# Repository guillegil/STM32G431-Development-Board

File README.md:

# STM32G431 Development Board

KiCad 10 design files for a small development board based on the STMicroelectronics
STM32G431CBT6 microcontroller (Cortex-M4F, 170 MHz, 128 KB flash, USB).

This is a personal learning project — my first custom-designed PCB, built as
preparation for a more complex nRF5340-based wireless keyboard development board.

## Features

- STM32G431CBT6 in LQFP-48 package (hand-solderable)
- USB-C connector for power and native USB device communication
- 3.3 V LDO regulator
- SWD programming header
- UART debug header
- User LED + user button
- Reset button + boot-mode jumper
- GPIO breakout headers for experimentation

## Project goals

- Learn KiCad 10 schematic and PCB design workflow
- Learn home reflow soldering (hot plate + hot air)
- Build a base for future Zephyr RTOS experimentation
- Prepare skills for a larger custom-keyboard project

## Status

🟡 In design — schematic in progress

## Tools used

- KiCad 10.x
- Zephyr RTOS / nRF Connect SDK (firmware, future)
- JLCPCB (PCB fabrication, planned)

## License

See [LICENSE](LICENSE). This project is open source under the MIT License.

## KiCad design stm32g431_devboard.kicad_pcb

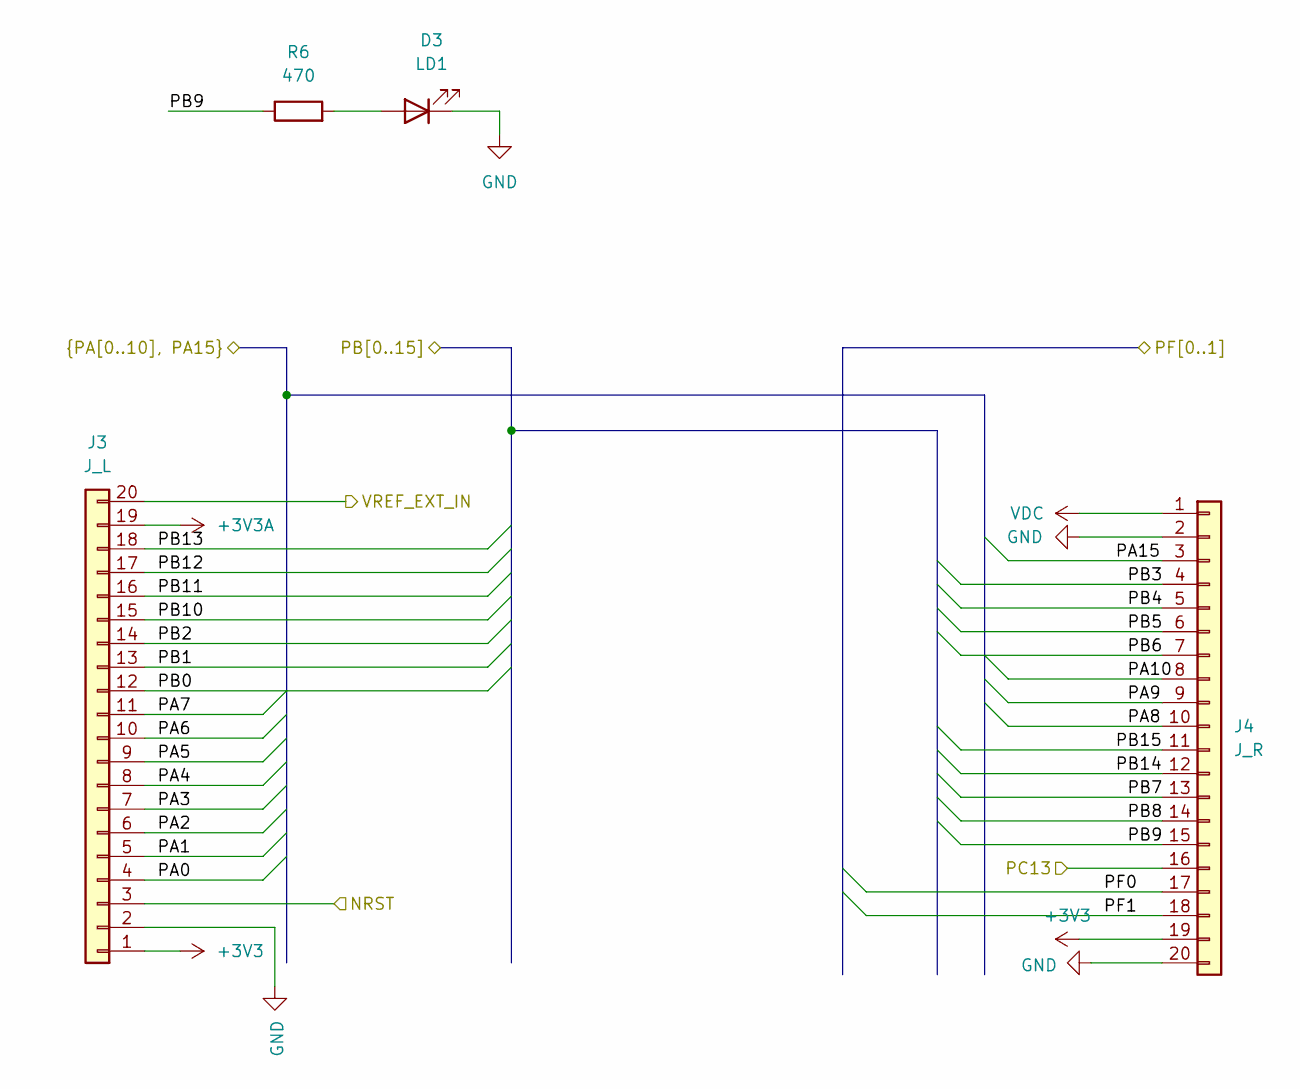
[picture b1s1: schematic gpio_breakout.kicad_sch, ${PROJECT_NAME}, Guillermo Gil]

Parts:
D3: LD1; LED_0603_1608Metric_Pad1.05x0.95mm_HandSolder
J3: J_L; PinHeader_1x20_P2.54mm_Vertical
J4: J_R; PinHeader_1x20_P2.54mm_Vertical
R6: 470; R_0603_1608Metric_Pad0.98x0.95mm_HandSolder

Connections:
+3V3: J3.1, J4.19; also elsewhere on the board
+3V3A: J3.19; also elsewhere on the board
/GPIO Breakout/PA0: J3.4; also elsewhere on the board
/GPIO Breakout/PA1: J3.5; also elsewhere on the board
/GPIO Breakout/PA2: J3.6; also elsewhere on the board
/GPIO Breakout/PA3: J3.7; also elsewhere on the board
/GPIO Breakout/PA4: J3.8; also elsewhere on the board
/GPIO Breakout/PA5: J3.9; also elsewhere on the board
/GPIO Breakout/PA6: J3.10; also elsewhere on the board
/GPIO Breakout/PA7: J3.11; also elsewhere on the board
/GPIO Breakout/PA8: J4.10; also elsewhere on the board
/GPIO Breakout/PA9: J4.9; also elsewhere on the board
/GPIO Breakout/PA10: J4.8; also elsewhere on the board
/GPIO Breakout/PA15: J4.3; also elsewhere on the board
/GPIO Breakout/PB0: J3.12; also elsewhere on the board
/GPIO Breakout/PB1: J3.13; also elsewhere on the board
/GPIO Breakout/PB2: J3.14; also elsewhere on the board
/GPIO Breakout/PB3: J4.4; also elsewhere on the board
/GPIO Breakout/PB4: J4.5; also elsewhere on the board
/GPIO Breakout/PB5: J4.6; also elsewhere on the board
/GPIO Breakout/PB6: J4.7; also elsewhere on the board
/GPIO Breakout/PB7: J4.13; also elsewhere on the board
/GPIO Breakout/PB8: J4.14; also elsewhere on the board
/GPIO Breakout/PB9: J4.15, R6.1; also elsewhere on the board
/GPIO Breakout/PB10: J3.15; also elsewhere on the board
/GPIO Breakout/PB11: J3.16; also elsewhere on the board
/GPIO Breakout/PB12: J3.17; also elsewhere on the board
/GPIO Breakout/PB13: J3.18; also elsewhere on the board
/GPIO Breakout/PB14: J4.12; also elsewhere on the board
/GPIO Breakout/PB15: J4.11; also elsewhere on the board
/GPIO Breakout/PF0: J4.17; also elsewhere on the board
/GPIO Breakout/PF1: J4.18; also elsewhere on the board
/GPIO Breakout/VREF_EXT_IN: J3.20; also elsewhere on the board
/MCU/NRST: J3.3; also elsewhere on the board
/MCU/PC13: J4.16; also elsewhere on the board
GND: D3.1 (K), J3.2, J4.2, J4.20; also elsewhere on the board
unnamed: D3.2 (A), R6.2
VDC: J4.1; also elsewhere on the board

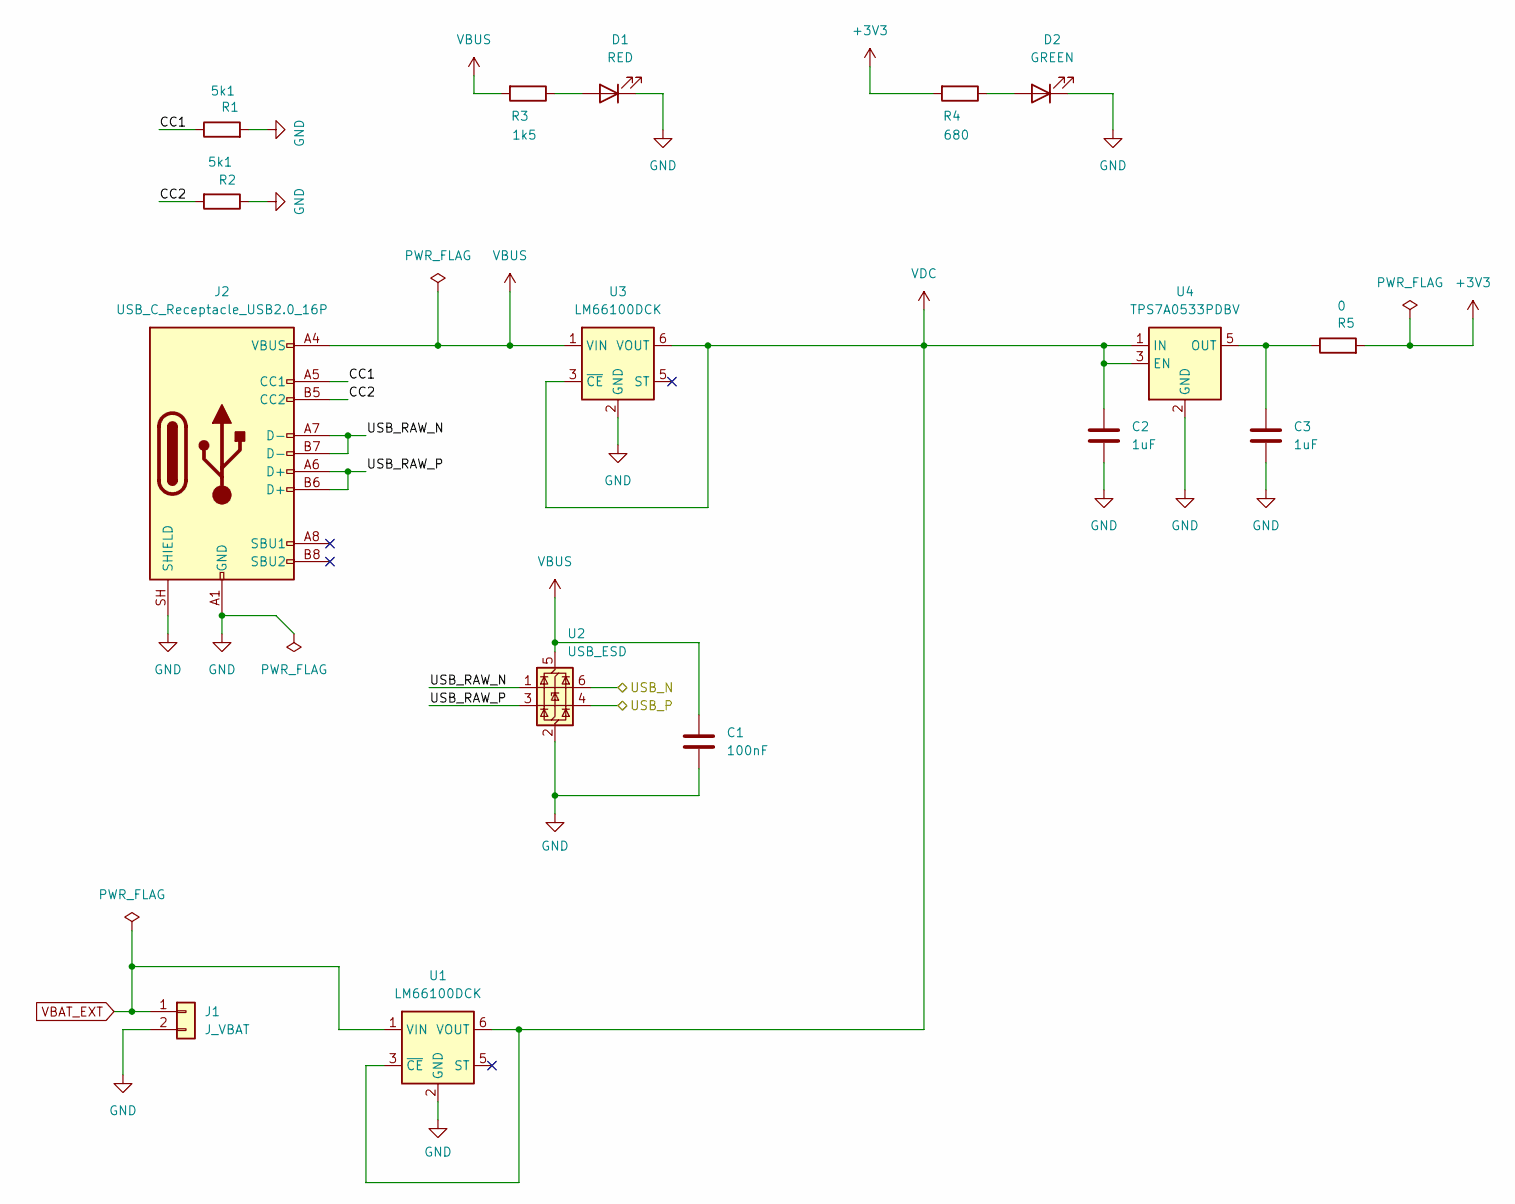
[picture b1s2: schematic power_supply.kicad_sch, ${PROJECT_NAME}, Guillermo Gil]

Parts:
C1: 100nF; C_0603_1608Metric_Pad1.08x0.95mm_HandSolder
C2, C3: 1uF; C_0603_1608Metric_Pad1.08x0.95mm_HandSolder
D1: RED; LED_0603_1608Metric_Pad1.05x0.95mm_HandSolder
D2: GREEN; LED_0603_1608Metric_Pad1.05x0.95mm_HandSolder
J1: J_VBAT; PinHeader_1x02_P2.54mm_Vertical
J2: USB_C_Receptacle_USB2.0_16P; USB_C_Receptacle_GCT_USB4085
R1, R2: 5k1; R_0603_1608Metric_Pad0.98x0.95mm_HandSolder
R3: 1k5; R_0603_1608Metric_Pad0.98x0.95mm_HandSolder
R4: 680; R_0603_1608Metric_Pad0.98x0.95mm_HandSolder
R5: 0; R_0603_1608Metric_Pad0.98x0.95mm_HandSolder
U1, U3: LM66100DCK; SOT-363_SC-70-6
U2: USB_ESD; SOT-23-6
U4: TPS7A0533PDBV; SOT-23-5_HandSoldering

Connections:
+3V3: R4.2, R5.2; also elsewhere on the board
/MCU/USB_N: U2.6 (I/O1); also elsewhere on the board
/MCU/USB_P: U2.4 (I/O2); also elsewhere on the board
/Power Supply/CC1: J2.A5 (CC1), R1.1
/Power Supply/CC2: J2.B5 (CC2), R2.2
/Power Supply/USB_RAW_N: J2.A7 (D-), J2.B7 (D-), U2.1 (I/O1)
/Power Supply/USB_RAW_P: J2.A6 (D+), J2.B6 (D+), U2.3 (I/O2)
GND: C1.2, C2.2, C3.2, D1.1 (K), D2.1 (K), J1.2, J2.A1 (GND), J2.A12 (GND), J2.B1 (GND), J2.B12 (GND), J2.SH (SHIELD), R1.2, R2.1, U1.2 (GND), U2.2 (GND), U3.2 (GND), U4.2 (GND); also elsewhere on the board
unnamed: D1.2 (A), R3.1
unnamed: D2.2 (A), R4.1
unnamed: C3.1, R5.1, U4.5 (OUT)
VBAT_EXT: J1.1, U1.1 (VIN)
VBUS: C1.1, J2.A4 (VBUS), J2.A9 (VBUS), J2.B4 (VBUS), J2.B9 (VBUS), R3.2, U2.5 (VBUS), U3.1 (VIN)
VDC: C2.1, U1.3 (~CE), U1.6 (VOUT), U3.3 (~CE), U3.6 (VOUT), U4.1 (IN), U4.3 (EN); also elsewhere on the board

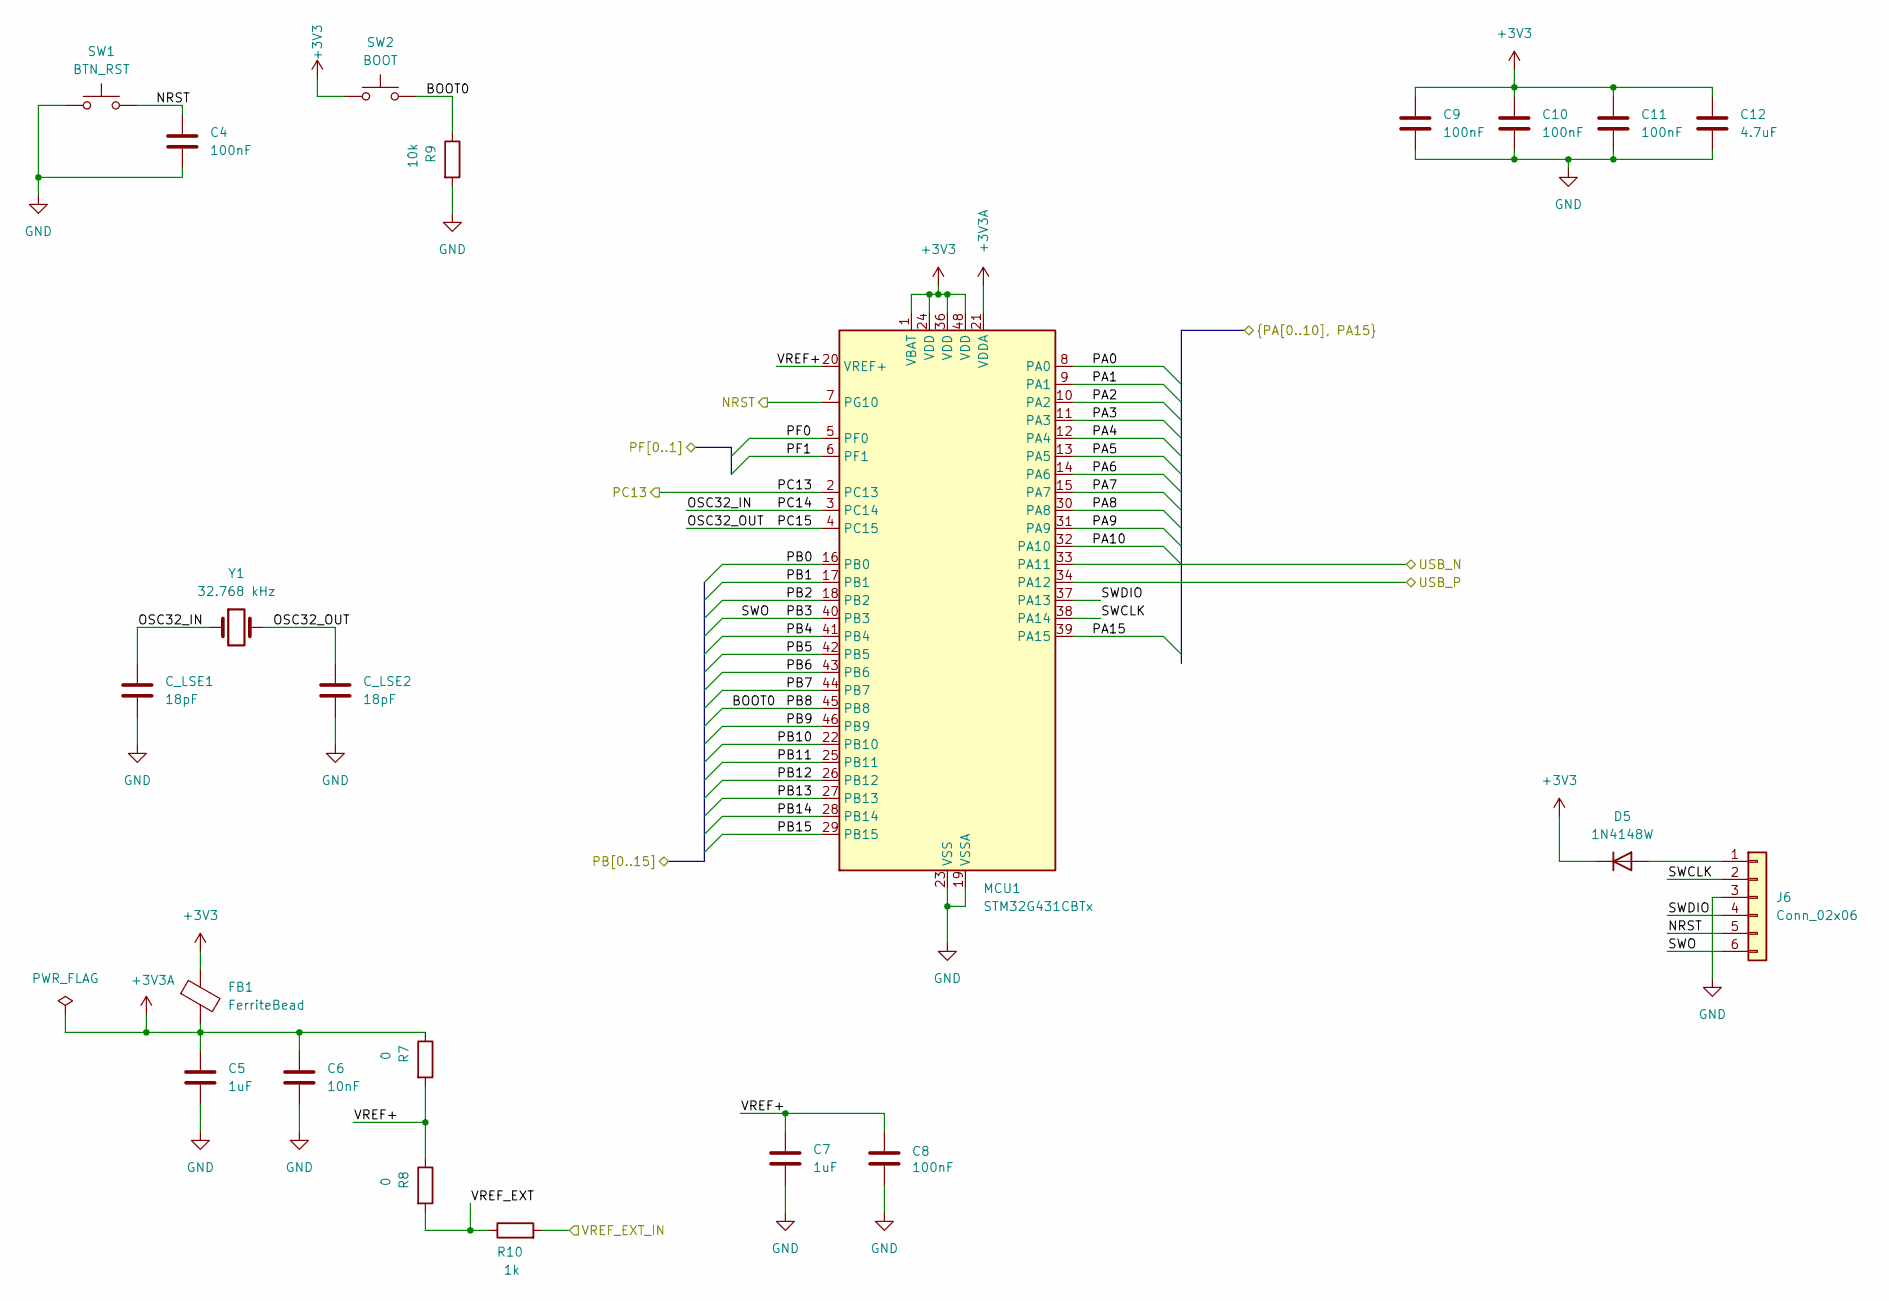
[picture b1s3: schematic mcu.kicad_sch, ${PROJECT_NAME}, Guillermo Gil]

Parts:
C4, C8, C9, C10, C11: 100nF; C_0603_1608Metric_Pad1.08x0.95mm_HandSolder
C5, C7: 1uF; C_0603_1608Metric_Pad1.08x0.95mm_HandSolder
C6: 10nF; C_0603_1608Metric_Pad1.08x0.95mm_HandSolder
C12: 4.7uF; C_0603_1608Metric_Pad1.08x0.95mm_HandSolder
C_LSE1, C_LSE2: 18pF; C_0603_1608Metric_Pad1.08x0.95mm_HandSolder
D5: 1N4148W; D_SOD-323
FB1: FerriteBead; L_0603_1608Metric_Pad1.05x0.95mm_HandSolder
J6: Conn_02x06; PinHeader_2x03_P2.54mm_Vertical_SMD
MCU1: STM32G431CBTx; LQFP-48_7x7mm_P0.5mm
R7, R8: 0; R_0603_1608Metric_Pad0.98x0.95mm_HandSolder
R9: 10k; R_0603_1608Metric_Pad0.98x0.95mm_HandSolder
R10: 1k; R_0603_1608Metric_Pad0.98x0.95mm_HandSolder
SW1: BTN_RST; SW_SPST_PTS810
SW2: BOOT; SW_SPST_PTS810
Y1: 32.768 kHz; Crystal_SMD_3215-2Pin_3.2x1.5mm

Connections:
+3V3: C9.1, C10.1, C11.1, C12.1, D5.1 (K), FB1.1, MCU1.1 (VBAT), MCU1.24 (VDD), MCU1.36 (VDD), MCU1.48 (VDD), SW2.1; also elsewhere on the board
+3V3A: C5.1, C6.1, FB1.2, MCU1.21 (VDDA), R7.1; also elsewhere on the board
/GPIO Breakout/PA0: MCU1.8 (PA0); also elsewhere on the board
/GPIO Breakout/PA1: MCU1.9 (PA1); also elsewhere on the board
/GPIO Breakout/PA2: MCU1.10 (PA2); also elsewhere on the board
/GPIO Breakout/PA3: MCU1.11 (PA3); also elsewhere on the board
/GPIO Breakout/PA4: MCU1.12 (PA4); also elsewhere on the board
/GPIO Breakout/PA5: MCU1.13 (PA5); also elsewhere on the board
/GPIO Breakout/PA6: MCU1.14 (PA6); also elsewhere on the board
/GPIO Breakout/PA7: MCU1.15 (PA7); also elsewhere on the board
/GPIO Breakout/PA8: MCU1.30 (PA8); also elsewhere on the board
/GPIO Breakout/PA9: MCU1.31 (PA9); also elsewhere on the board
/GPIO Breakout/PA10: MCU1.32 (PA10); also elsewhere on the board
/GPIO Breakout/PA15: MCU1.39 (PA15); also elsewhere on the board
/GPIO Breakout/PB0: MCU1.16 (PB0); also elsewhere on the board
/GPIO Breakout/PB1: MCU1.17 (PB1); also elsewhere on the board
/GPIO Breakout/PB2: MCU1.18 (PB2); also elsewhere on the board
/GPIO Breakout/PB3: J6.6, MCU1.40 (PB3); also elsewhere on the board
/GPIO Breakout/PB4: MCU1.41 (PB4); also elsewhere on the board
/GPIO Breakout/PB5: MCU1.42 (PB5); also elsewhere on the board
/GPIO Breakout/PB6: MCU1.43 (PB6); also elsewhere on the board
/GPIO Breakout/PB7: MCU1.44 (PB7); also elsewhere on the board
/GPIO Breakout/PB8: MCU1.45 (PB8), R9.1, SW2.2; also elsewhere on the board
/GPIO Breakout/PB9: MCU1.46 (PB9); also elsewhere on the board
/GPIO Breakout/PB10: MCU1.22 (PB10); also elsewhere on the board
/GPIO Breakout/PB11: MCU1.25 (PB11); also elsewhere on the board
/GPIO Breakout/PB12: MCU1.26 (PB12); also elsewhere on the board
/GPIO Breakout/PB13: MCU1.27 (PB13); also elsewhere on the board
/GPIO Breakout/PB14: MCU1.28 (PB14); also elsewhere on the board
/GPIO Breakout/PB15: MCU1.29 (PB15); also elsewhere on the board
/GPIO Breakout/PF0: MCU1.5 (PF0); also elsewhere on the board
/GPIO Breakout/PF1: MCU1.6 (PF1); also elsewhere on the board
/GPIO Breakout/VREF_EXT_IN: R10.2; also elsewhere on the board
/MCU/NRST: C4.1, J6.5, MCU1.7 (PG10), SW1.2; also elsewhere on the board
/MCU/OSC32_IN: C_LSE1.1, MCU1.3 (PC14), Y1.1
/MCU/OSC32_OUT: C_LSE2.1, MCU1.4 (PC15), Y1.2
/MCU/PC13: MCU1.2 (PC13); also elsewhere on the board
/MCU/SWCLK: J6.2, MCU1.38 (PA14)
/MCU/SWDIO: J6.4, MCU1.37 (PA13)
/MCU/USB_N: MCU1.33 (PA11); also elsewhere on the board
/MCU/USB_P: MCU1.34 (PA12); also elsewhere on the board
/MCU/VREF+: C7.1, C8.1, MCU1.20 (VREF+), R7.2, R8.1
/MCU/VREF_EXT: R8.2, R10.1
GND: C4.2, C5.2, C6.2, C7.2, C8.2, C9.2, C10.2, C11.2, C12.2, C_LSE1.2, C_LSE2.2, J6.3, MCU1.19 (VSSA), MCU1.23 (VSS), MCU1.35 (VSS), MCU1.47 (VSS), R9.2, SW1.1; also elsewhere on the board
unnamed: D5.2 (A), J6.1

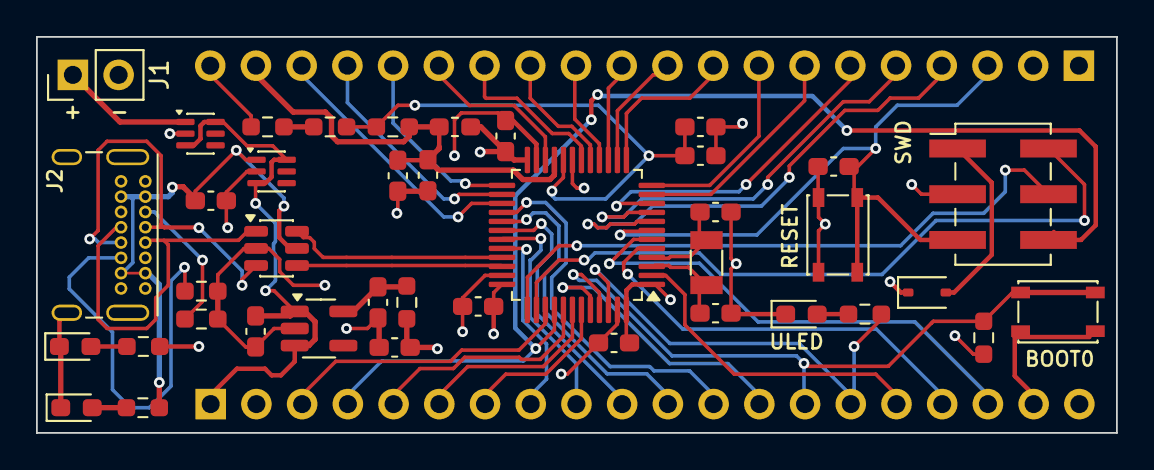
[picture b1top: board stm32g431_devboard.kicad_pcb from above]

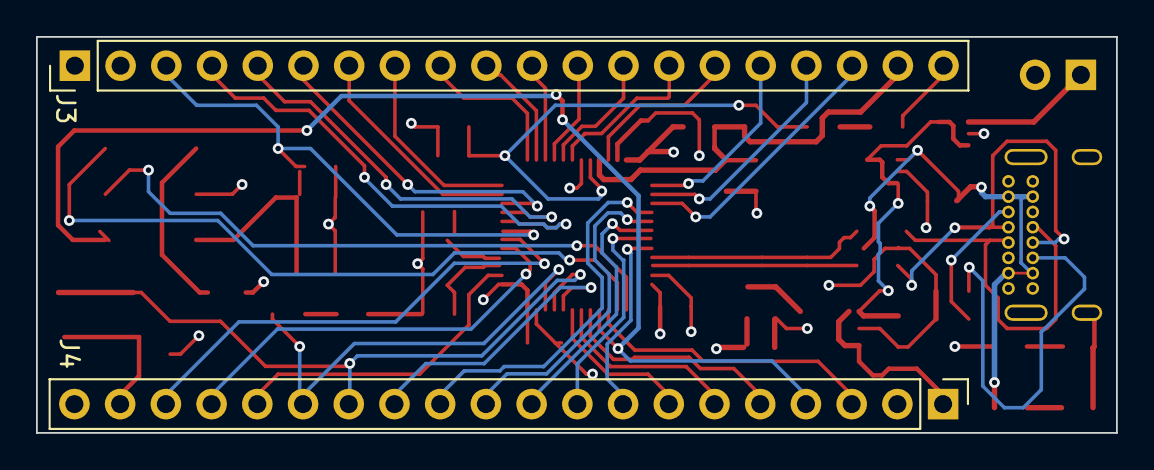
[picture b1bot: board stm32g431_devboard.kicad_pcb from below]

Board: 4 copper layers, 60.0 x 22.0 mm, 42 parts (2 on the bottom side), 56 nets.

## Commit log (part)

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2026-05-17 Initial project structure
2026-05-17 Place STM32G431CBTx MCU symbol
2026-05-17 Modify Readme.md
2026-05-17 Add License
2026-05-17 Add: Power Supply hierarchical sheet
2026-05-18 Add dual-LDO selector, power LEDs, current measurement jumper
2026-05-18 Complete MCU power, debug, and boot circuits; add scope doc
    Schematic additions:
    - Add second Schottky on USB VBUS for full diode-OR protection
    - Wire VBAT, VSS, VSSA to power nets
    - Add VDD decoupling: 3x 100nF + 1x 4.7uF bulk
    - Add VDDA filter: ferrite bead + 1uF + 10nF
    - Add VREF+ selector jumper with decoupling and external input
2026-05-19 feat(schematic): complete v0.1 schematic for STM32G431 dev board
    Three-sheet hierarchical design with clean ERC pass (0 errors, 0 warnings).
    MCU (mcu.kicad_sch):
    - STM32G431CBTx LQFP-48
    - VDD decoupling (3× 100nF + 1× 4.7µF)
    - VDDA filter via ferrite bead + 1µF + 10nF
    - VREF+ selector jumper (internal +3V3A or external via 1kΩ series)
2026-05-19 Created PCB editor, configure for JLCPCB standards
    Additionally, created a specific library for castellard jumpers
2026-05-20 Started PCB placing
2026-05-20 v0.2: low-power redesign — single LDO, ideal diodes, LSE, castellated SWD
    Power supply:
    - Replace dual LDO (AP2112K + MCP1700) with single TPS7A0233PDBV
    (25 nA Iq nanopower; EN tied to IN per datasheet)
    - Replace SS14 Schottky diodes with LM66100 ideal diode controllers
    in diode-OR configuration (CE tied to VOUT for RCB mode)
    - Remove jumpers J2 (LDO_SEL), J3 (LED_VBUS), J4 (LED_3V3)
2026-05-25 Finish routing
